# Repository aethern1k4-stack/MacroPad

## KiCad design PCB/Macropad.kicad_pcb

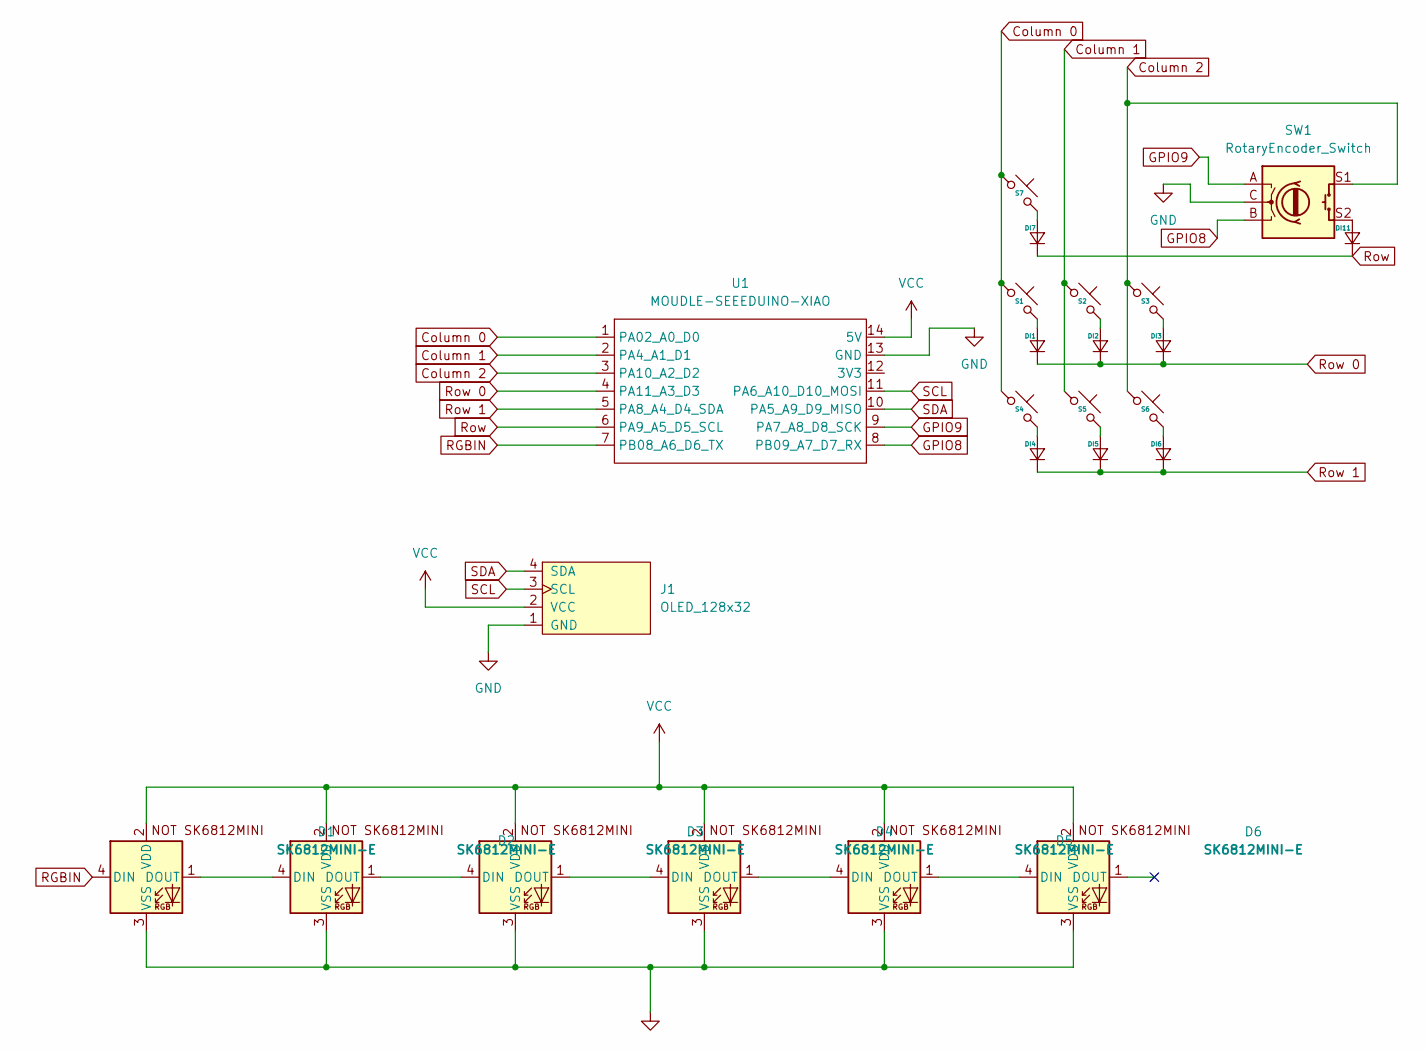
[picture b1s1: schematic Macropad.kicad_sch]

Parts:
D1, D2, D3, D4, D5, D6: SK6812MINI-E; LED_SK6812MINI
DI1, DI2, DI3, DI4, DI5, DI6, DI7, DI11: D_DO-35_SOD27_P10.16mm_Horizontal
J1: OLED_128x32
S1, S2, S3, S4, S5, S6, S7: SW_Cherry_MX_1.00u_PCB
SW1: RotaryEncoder_Switch; RotaryEncoder_Alps_EC11E-Switch_Vertical_H20mm
U1: MOUDLE-SEEEDUINO-XIAO; XIAO-Generic-Hybrid-14P-2.54-21X17.8MM

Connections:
Column 0: S1.1, S4.1, S7.1, U1.1 (PA02_A0_D0)
Column 1: S2.1, S5.1, U1.2 (PA4_A1_D1)
Column 2: S3.1, S6.1, SW1.S1, U1.3 (PA10_A2_D2)
GND: D1.3 (VSS), D2.3 (VSS), D3.3 (VSS), D4.3 (VSS), D5.3 (VSS), D6.3 (VSS), J1.1 (GND), SW1.C, U1.13 (GND)
GPIO8: SW1.B, U1.8 (PB09_A7_D7_RX)
GPIO9: SW1.A, U1.9 (PA7_A8_D8_SCK)
unnamed: D1.1 (DOUT), D2.4 (DIN)
unnamed: D2.1 (DOUT), D3.4 (DIN)
unnamed: D3.1 (DOUT), D4.4 (DIN)
unnamed: D4.1 (DOUT), D5.4 (DIN)
unnamed: D5.1 (DOUT), D6.4 (DIN)
unnamed: DI1.2 (A), S1.2
unnamed: DI2.2 (A), S2.2
unnamed: DI3.2 (A), S3.2
unnamed: DI4.2 (A), S4.2
unnamed: DI5.2 (A), S5.2
unnamed: DI6.2 (A), S6.2
unnamed: DI7.2 (A), S7.2
unnamed: DI11.2 (A), SW1.S2
RGBIN: D1.4 (DIN), U1.7 (PB08_A6_D6_TX)
Row: DI7.1 (K), DI11.1 (K), U1.6 (PA9_A5_D5_SCL)
Row 0: DI1.1 (K), DI2.1 (K), DI3.1 (K), U1.4 (PA11_A3_D3)
Row 1: DI4.1 (K), DI5.1 (K), DI6.1 (K), U1.5 (PA8_A4_D4_SDA)
SCL: J1.3 (SCL), U1.11 (PA6_A10_D10_MOSI)
SDA: J1.4 (SDA), U1.10 (PA5_A9_D9_MISO)
VCC: D1.2 (VDD), D2.2 (VDD), D3.2 (VDD), D4.2 (VDD), D5.2 (VDD), D6.2 (VDD), J1.2 (VCC), U1.14 (5V)

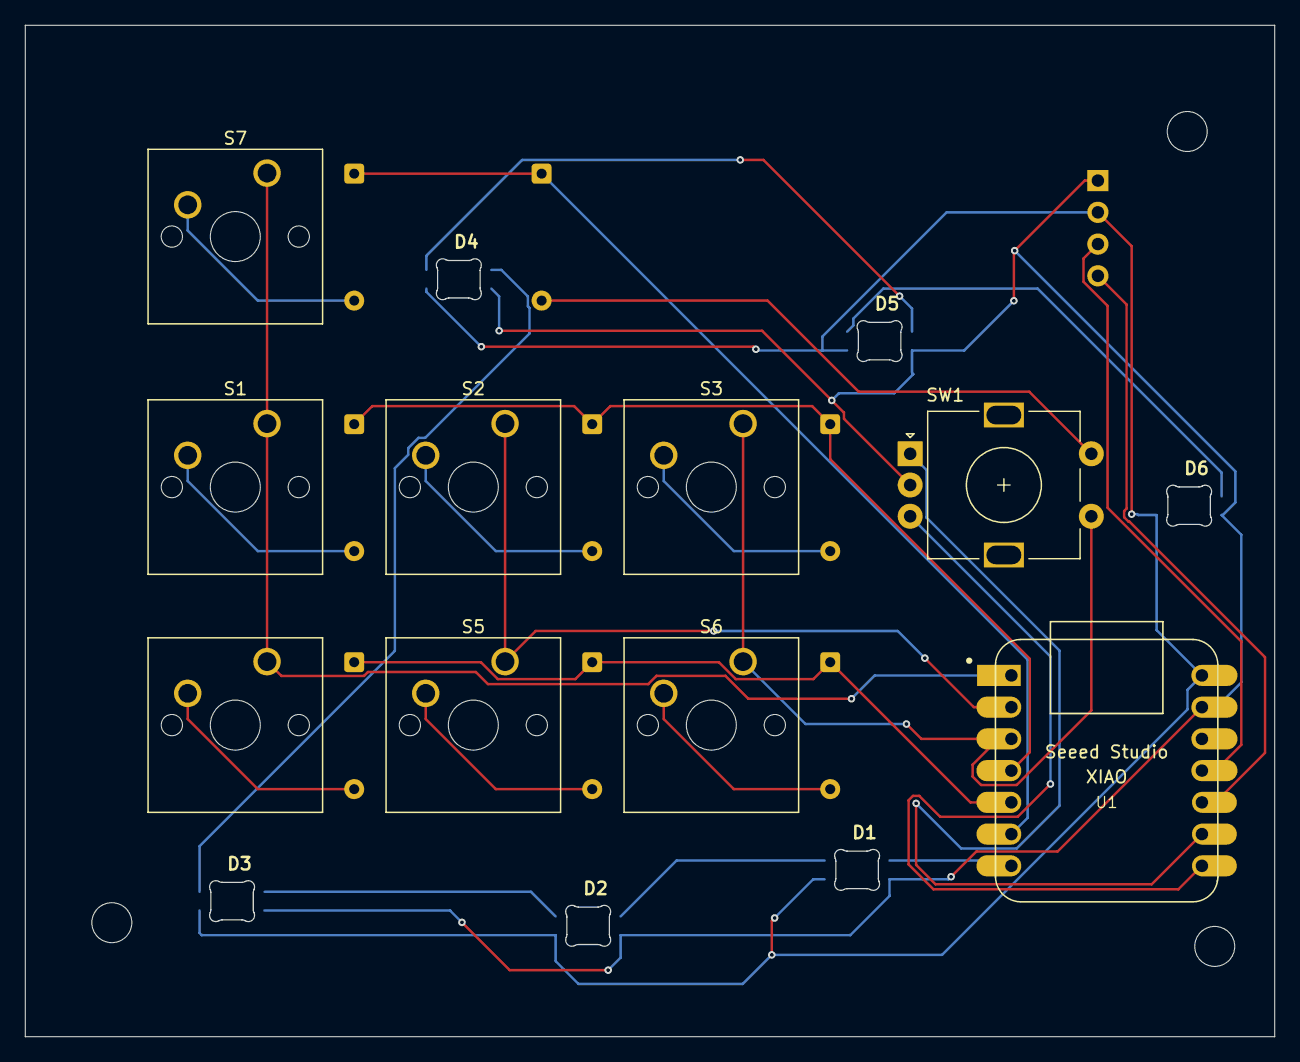
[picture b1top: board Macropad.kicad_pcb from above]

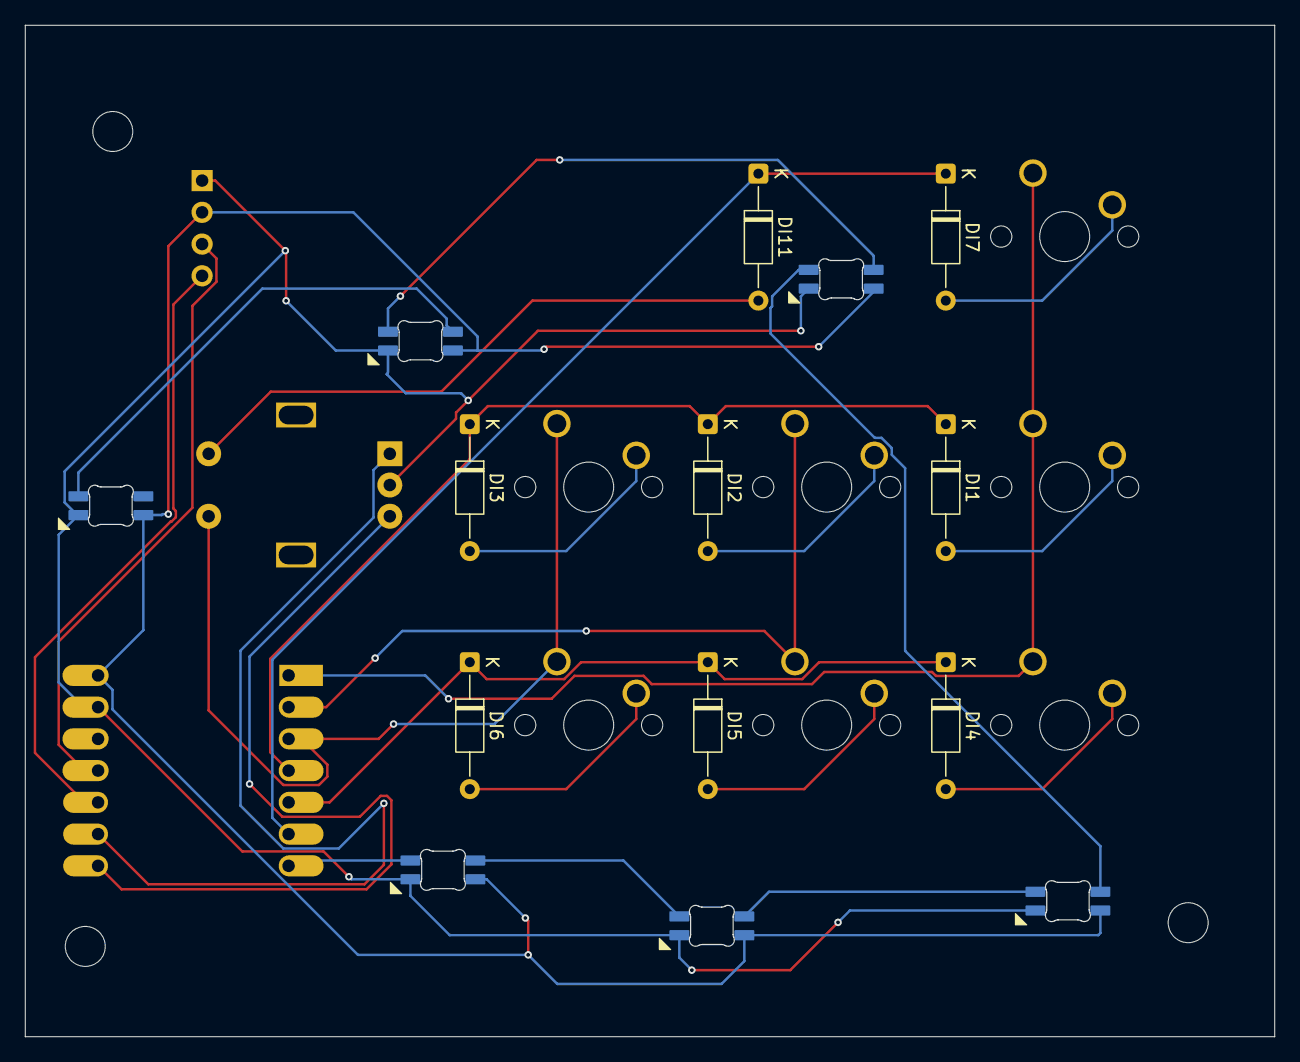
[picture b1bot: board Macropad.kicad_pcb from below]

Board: 2 copper layers, 100.0 x 80.9 mm, 24 parts (8 on the bottom side), 26 nets.

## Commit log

2026-03-10 PCB parts addition
    PCB parts and files are now all added.
2026-03-13 replalced exxisting files
